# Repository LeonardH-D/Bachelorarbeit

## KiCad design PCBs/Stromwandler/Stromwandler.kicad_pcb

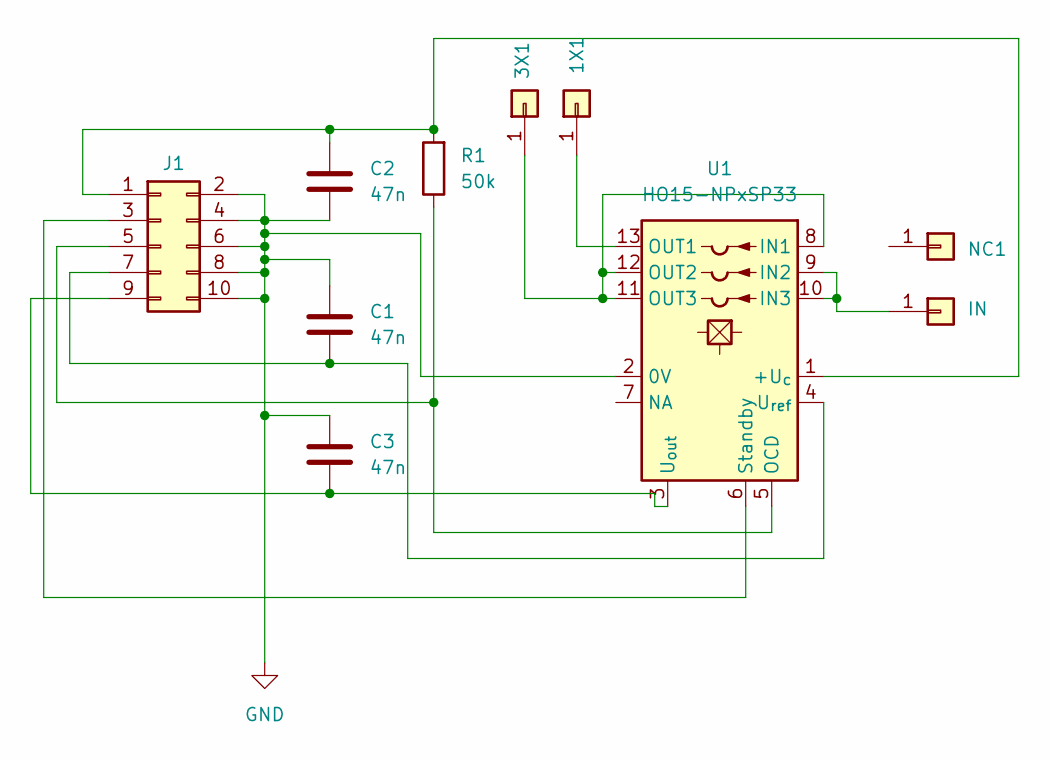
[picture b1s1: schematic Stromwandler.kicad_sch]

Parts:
1X1, 3X1: Conn_01x01; MountingHole_4.3mm_M4_DIN965_Pad
C1, C2, C3: 47n; C_0805_2012Metric_Pad1.18x1.45mm_HandSolder
J1: Conn_02x05_Odd_Even; PinHeader_2x05_P2.54mm_Vertical
J4: IN; MountingHole_4.3mm_M4_DIN965_Pad
NC1: Conn_01x01; MountingHole_4.3mm_M4_DIN965_Pad
R1: 50k; R_0805_2012Metric
U1: HO15-NPxSP33; LEM_HO8-NP

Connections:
GND: C1.1, C2.2, C3.1, J1.2, J1.4, J1.6, J1.8, J1.10, U1.2 (0V)
unnamed: 1X1.1 (Pin_1_1), U1.13 (OUT1)
unnamed: 3X1.1 (Pin_1_1), U1.8 (IN1), U1.11 (OUT3), U1.12 (OUT2)
unnamed: C2.1, J1.1, R1.2, U1.1 (+U_{c})
unnamed: J1.3, U1.6 (Standby)
unnamed: J1.5, R1.1, U1.5 (OCD)
unnamed: C1.2, J1.7, U1.4 (U_{ref})
unnamed: C3.2, J1.9, U1.3 (U_{out})
unnamed: J4.1 (Pin_1_1), U1.9 (IN2), U1.10 (IN3)

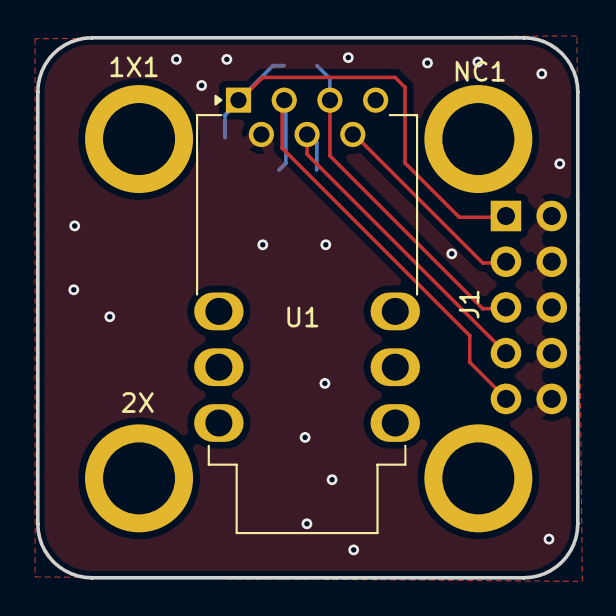
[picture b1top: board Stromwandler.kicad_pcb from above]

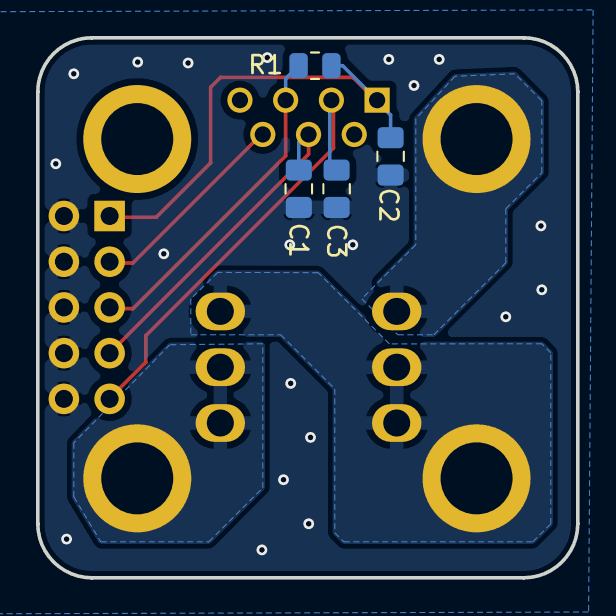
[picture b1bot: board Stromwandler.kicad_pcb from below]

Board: 2 copper layers, 30.0 x 30.0 mm, 10 parts (4 on the bottom side), 9 nets.

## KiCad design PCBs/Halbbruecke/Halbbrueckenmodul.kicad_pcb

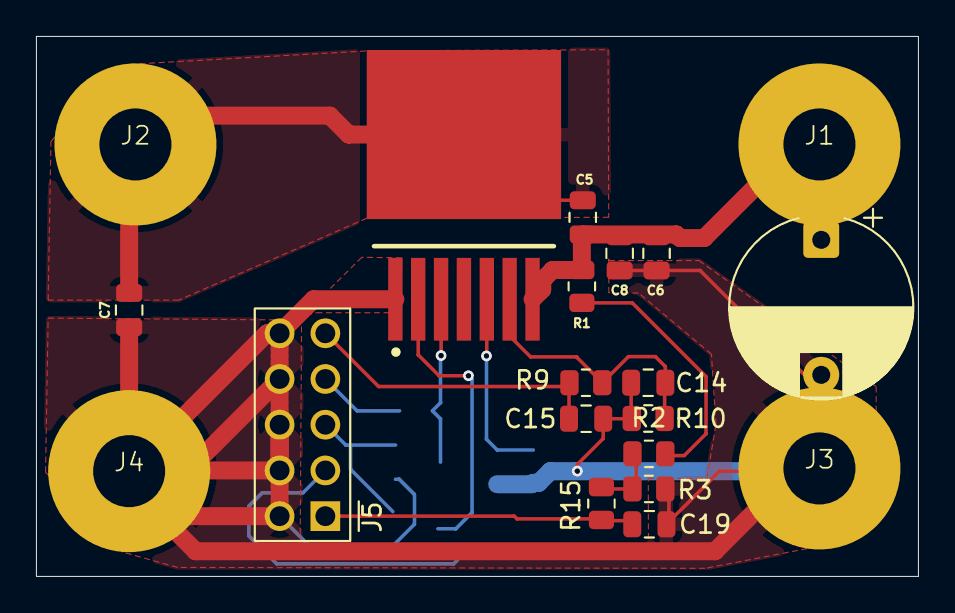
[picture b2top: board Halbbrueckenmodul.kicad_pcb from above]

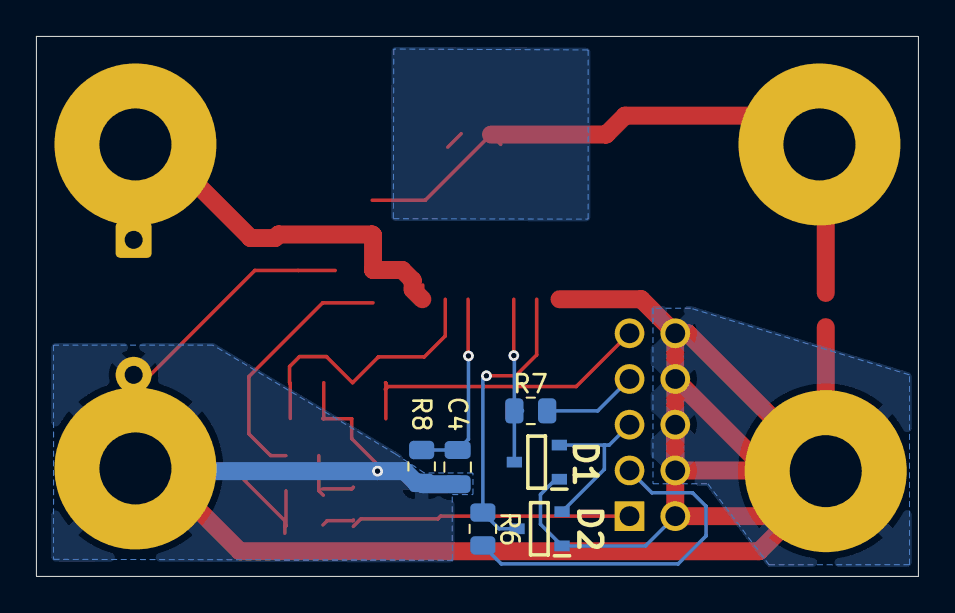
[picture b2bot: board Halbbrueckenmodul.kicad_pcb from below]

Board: 2 copper layers, 49.0 x 30.0 mm, 26 parts (6 on the bottom side), 14 nets.

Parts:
C4, C6, C8: 100nF; C_0805_2012Metric
C5: C220nF; C_0805_2012Metric
C7: 220nF; C_0805_2012Metric
C14, C15, C19: 10nF; C_0805_2012Metric
C1800: 220uF; CP_Radial_D10.0mm_P7.50mm
D1, D2: BAT_64-04_E6327; BAT64-04
IC1: IFX007TAUMA1
J1: +ZK; Lötpad_rund_mit_Loch
J2: OUT; Lötpad_rund_mit_Loch
J3: GND; Lötpad_rund_mit_Loch
J4: GND1; Lötpad_rund_mit_Loch
J5: Stifteiste_10_Pol___61301021121; Stifleiste_10_Pol
R1, R2: 30kΩ; R_0805_2012Metric
R3: 6.8kΩ; R_0805_2012Metric
R6, R7: 10kOhm; R_0805_2012Metric
R8: 510Ohm; R_0805_2012Metric
R9, R10: 1kΩ; R_0805_2012Metric
R15: 100kΩ; R_0805_2012Metric

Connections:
5V: D1.2 (K2), D2.2 (K2), J5.5
+ZK: C5.2, C6.1, C8.1, C1800.1, IC1.7 (VS), J1.1, R1.1
GND: C4.2, C6.2, C7.1, C8.2, C14.2, C15.2, C19.2, C1800.2, D1.1 (A1), D2.1 (A1), IC1.1 (GND), J3.1, J4.1, J5.2, J5.4, J5.6, J5.8, J5.10, R3.2, R8.2, R10.2
I: C15.1, J5.9, R9.2
IN: J5.3, R6.1
INH: J5.7, R7.1
IS1: C14.1, IC1.6 (IS), R9.1, R10.1
unnamed: D1.3 (K1/A2), IC1.3 (INH), R7.2
unnamed: D2.3 (K1/A2), IC1.2 (IN), R6.2
unnamed: C4.1, IC1.5 (SR), R8.1
unnamed: R1.2, R2.1
unnamed: R2.2, R3.1, R15.1
OUT: C5.1, C7.2, IC1.8 (OUT_2), J2.1
UZK: C19.1, J5.1, R15.2

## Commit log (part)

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2026-05-13 Erster Upload
    Erster Upload
2026-05-13 Halbbruecke
    Erster Upload der PCB
2026-05-20 Create Halbbrueckenmodul.kicad_sch
    Schematic
2026-05-20 unnoetige Dateien entfernt
2026-05-21 Anpassungen
    GND Fill und Tausch von Signal und Leistungsseite
2026-05-24 Test with smaller holes, bottom only; to avoid DRC errors
2026-05-27 Zusammenfuehrung
    PCB und SCH Update zu 7-polig. Mehr übersichtlichkeit und Update Footprints Connectoren
2026-05-27 Korrekturen: Anordnung 4mm-Pins Tausch Stecker Pin 5 7 (Uref, OCD) GND Vias (noch mehr notwendig / Anordnung pruefen)
2026-05-27 Vias und R
    Neue platzierung von Vias und R.
2026-06-25 Berechnungen Auslaufversuch
2026-06-28 Upload STLs und STEPs
    Das sind alle notwendigen STLs zum Drucken und STEPS zur weiterbearbeitung. Die Anzahl welche benötigt werden stehen bei den STLs dahinter, sowie das Material. Falls kein Material dabei steht einfach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
